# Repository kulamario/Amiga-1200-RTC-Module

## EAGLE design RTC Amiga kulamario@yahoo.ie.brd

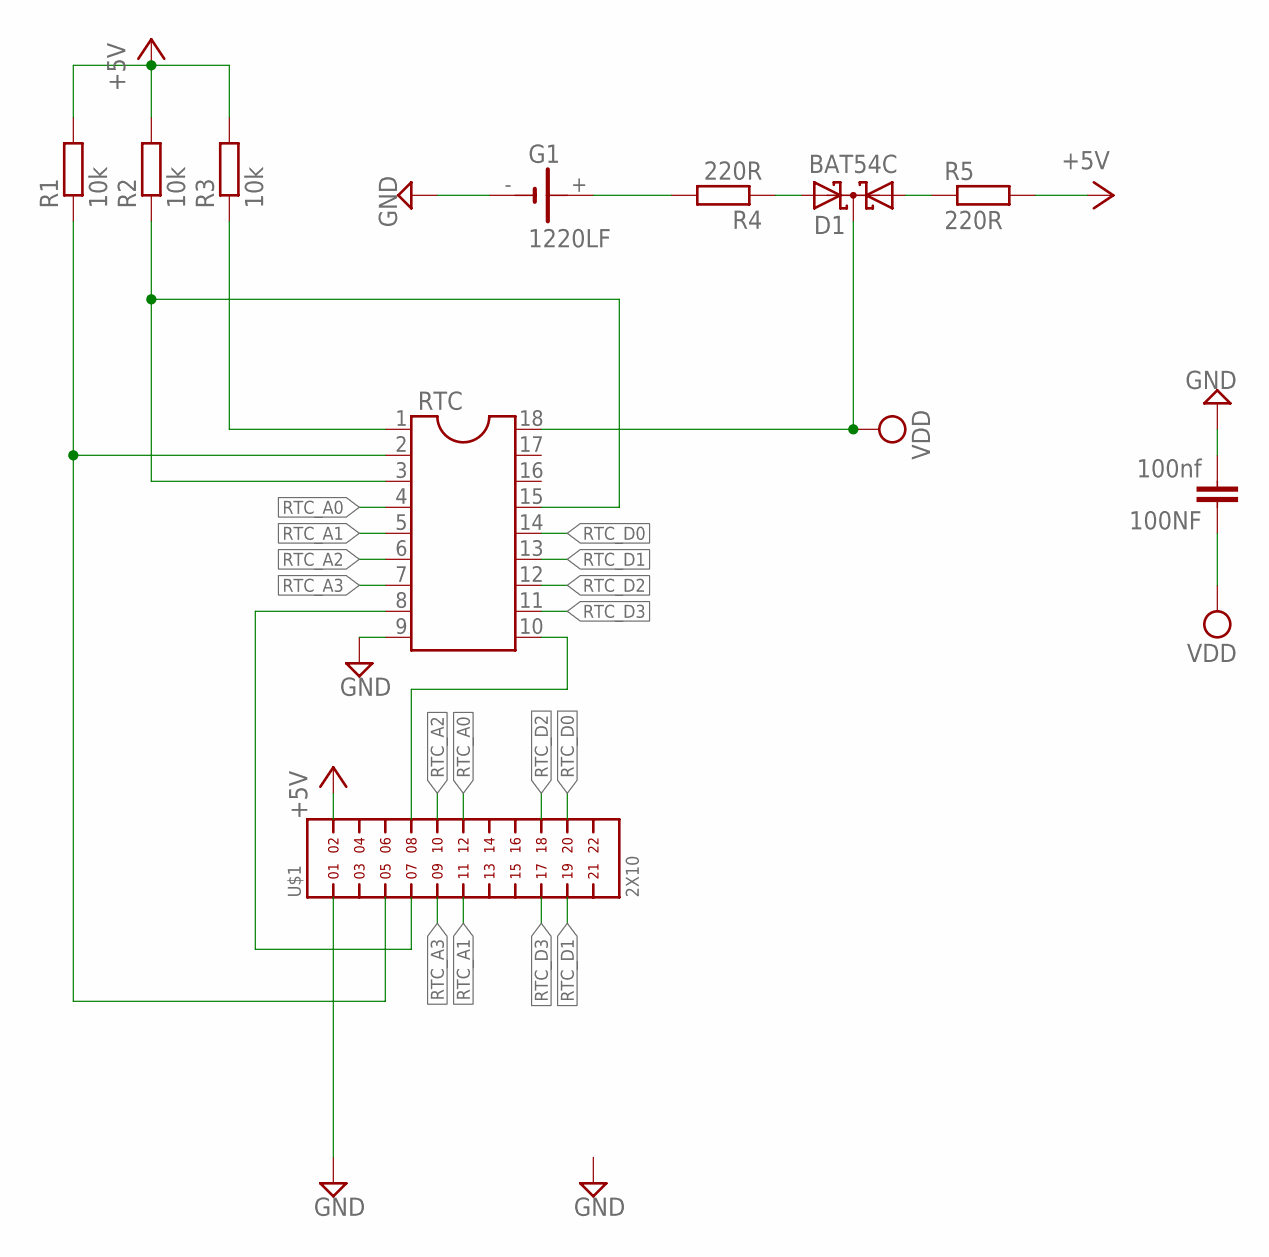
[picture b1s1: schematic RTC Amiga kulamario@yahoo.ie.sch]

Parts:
100NF: 100nf; C0603
D1: BAT54C; SOT23
G1: 1220LF; CH291-1220LF
R1, R2, R3: 10k; R0603
R4, R5: 220R; R0603
RTC: DIL18
U$1: 2X10

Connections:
+5V: R1.2, R2.2, R3.2, R5.2, U$1.2
GND: 100NF.2, G1.-, RTC.9, U$1.1
unnamed: D1.1 (A1), R5.1
unnamed: D1.2 (A2), R4.1
unnamed: R3.1, RTC.1
unnamed: R1.1, RTC.2, U$1.5
unnamed: RTC.8, U$1.7
unnamed: RTC.10, U$1.8
unnamed: R2.1, RTC.3, RTC.15
unnamed: G1.+, R4.2
RTC_A0: RTC.4, U$1.12
RTC_A1: RTC.5, U$1.11
RTC_A2: RTC.6, U$1.10
RTC_A3: RTC.7, U$1.9
RTC_D0: RTC.14, U$1.20
RTC_D1: RTC.13, U$1.19
RTC_D2: RTC.12, U$1.18
RTC_D3: RTC.11, U$1.17
VDD: 100NF.1, D1.3 (CC), RTC.18

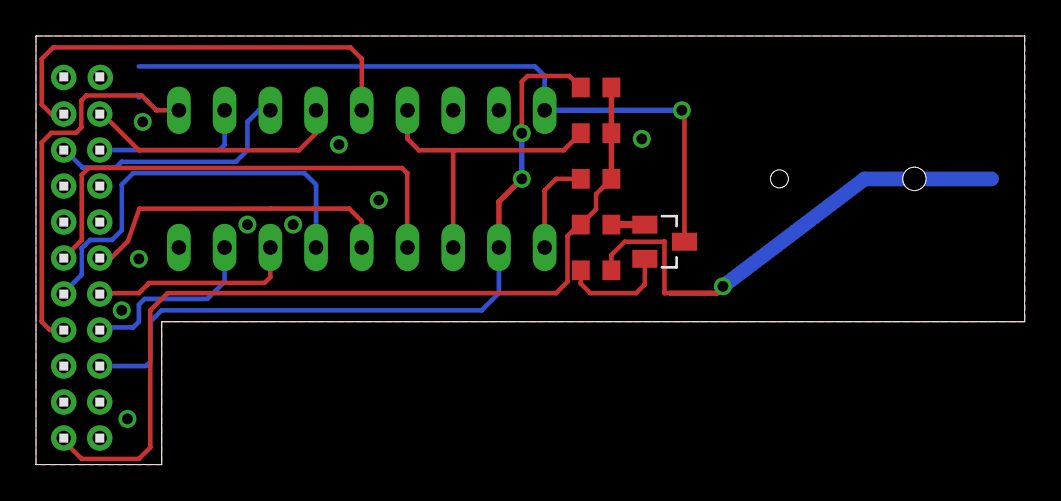
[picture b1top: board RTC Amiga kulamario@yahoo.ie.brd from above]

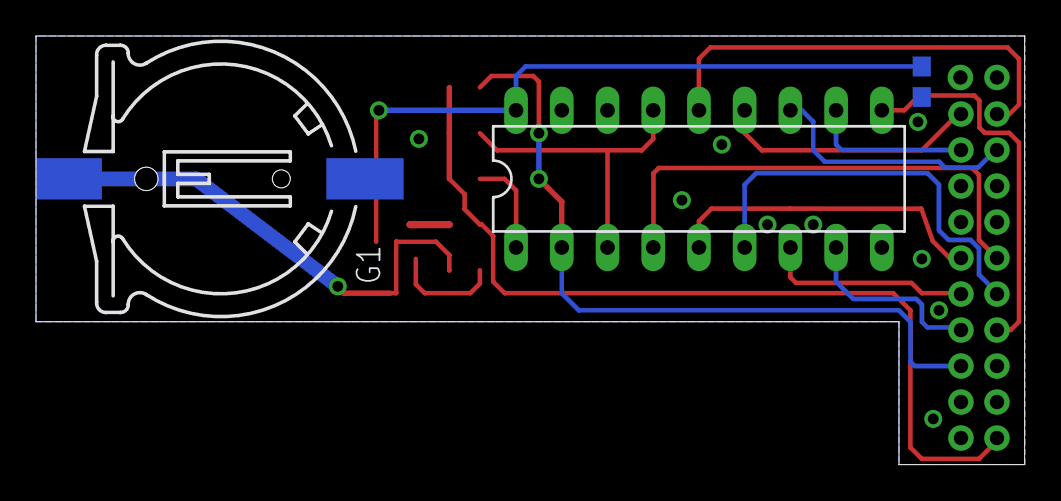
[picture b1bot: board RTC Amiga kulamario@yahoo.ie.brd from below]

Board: 2 copper layers, 54.9 x 23.8 mm, 10 parts (3 on the bottom side), 19 nets.
